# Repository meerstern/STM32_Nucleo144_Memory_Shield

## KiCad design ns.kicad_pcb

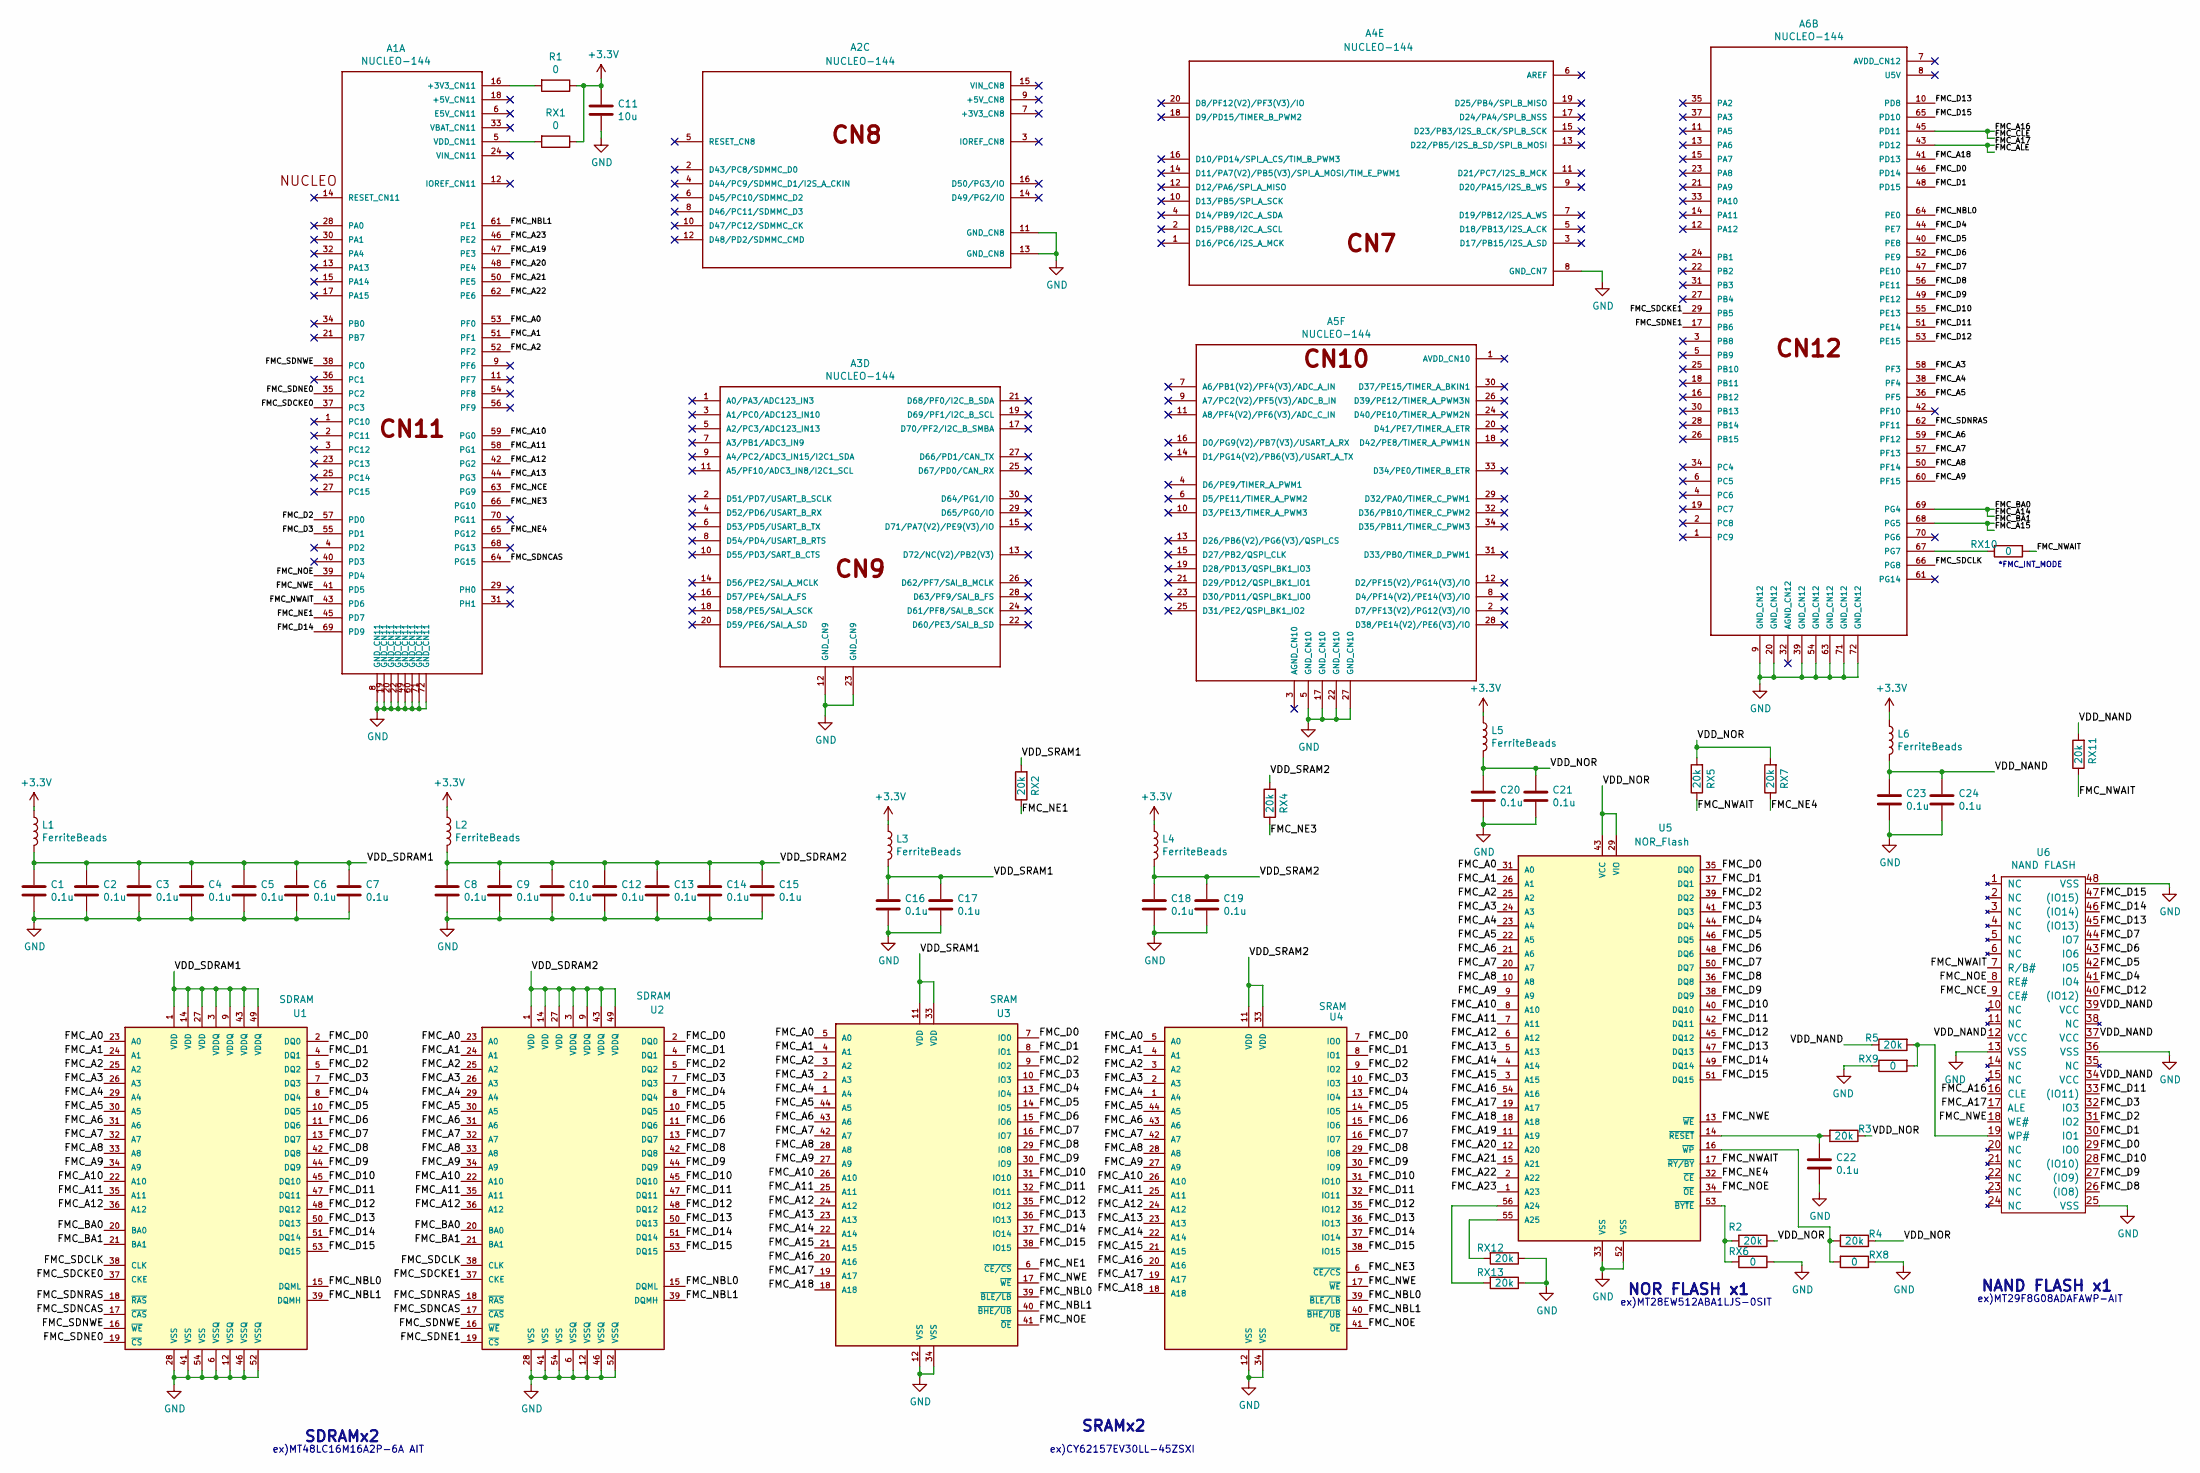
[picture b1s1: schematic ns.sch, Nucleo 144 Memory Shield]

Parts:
A1, A6: NUCLEO-144; PinSocket_2x36_P2.54mm_Vertical
A2: NUCLEO-144; PinSocket_2x08_P2.54mm_Vertical
A3: NUCLEO-144; PinSocket_2x15_P2.54mm_Vertical
A4: NUCLEO-144; PinSocket_2x10_P2.54mm_Vertical
A5: NUCLEO-144; PinSocket_2x17_P2.54mm_Vertical
C1, C2, C3, C4, C5, C6, C7, C8, C9, C10, C12, C13, C14, C15, C16, C17, C18, C19, C20, C21, C22, C23, C24: 0.1u; C_0603_1608Metric
C11: 10u; C_0805_2012Metric
L1, L2, L3, L4, L5, L6: FerriteBeads; L_0603_1608Metric
R1: 0; R_0603_1608Metric
R2, R3, R4, R5: 20k; R_0603_1608Metric
RX1, RX6, RX8, RX9, RX10: 0; R_0603_1608Metric
RX2, RX4, RX5, RX7, RX11, RX12, RX13: 20k; R_0603_1608Metric
U1, U2: SDRAM; TSOP-II-54_22.2x10.16mm_P0.8mm
U3, U4: SRAM; TSOP-II-44_10.16x18.41mm_P0.8mm
U5: NOR_Flash; TSOP-I-56_18.4x14mm_P0.5mm
U6: NAND FLASH; TSOP-I-48_18.4x12mm_P0.5mm

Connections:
+3V3: C11.1, L1.1, L2.1, L3.1, L4.1, L5.1, L6.1, R1.1, RX1.1
/FMC_A0: A1.53 (PF0), U1.23 (A0), U2.23 (A0), U3.5 (A0), U4.5 (A0), U5.31 (A0)
/FMC_A1: A1.51 (PF1), U1.24 (A1), U2.24 (A1), U3.4 (A1), U4.4 (A1), U5.26 (A1)
/FMC_A2: A1.52 (PF2), U1.25 (A2), U2.25 (A2), U3.3 (A2), U4.3 (A2), U5.25 (A2)
/FMC_A3: A6.58 (PG1), U1.26 (A3), U2.26 (A3), U3.2 (A3), U4.2 (A3), U5.24 (A3)
/FMC_A4: A6.38 (PC0), U1.29 (A4), U2.29 (A4), U3.1 (A4), U4.1 (A4), U5.23 (A4)
/FMC_A5: A6.36 (PC1), U1.30 (A5), U2.30 (A5), U3.44 (A5), U4.44 (A5), U5.22 (A5)
/FMC_A6: A6.59 (PG0), U1.31 (A6), U2.31 (A6), U3.43 (A6), U4.43 (A6), U5.21 (A6)
/FMC_A7: A6.57 (PD0), U1.32 (A7), U2.32 (A7), U3.42 (A7), U4.42 (A7), U5.20 (A7)
/FMC_A8: A6.50 (PE5), U1.33 (A8), U2.33 (A8), U3.28 (A8), U4.28 (A8), U5.10 (A8)
/FMC_A9: A6.60 (GND_CN11), U1.34 (A9), U2.34 (A9), U3.27 (A9), U4.27 (A9), U5.9 (A9)
/FMC_A10: A1.59 (PG0), U1.22 (A10), U2.22 (A10), U3.26 (A10), U4.26 (A10), U5.8 (A10)
/FMC_A11: A1.58 (PG1), U1.35 (A11), U2.35 (A11), U3.25 (A11), U4.25 (A11), U5.7 (A11)
/FMC_A12: A1.42 (PG2), U1.36 (A12), U2.36 (A12), U3.24 (A12), U4.24 (A12), U5.6 (A12)
/FMC_A13: A1.44 (PG3), U3.23 (A13), U4.23 (A13), U5.5 (A13)
/FMC_A14: A6.69 (PD9), U1.20 (BA0), U2.20 (BA0), U3.22 (A14), U4.22 (A14), U5.4 (A14)
/FMC_A15: A6.68 (PG13), U1.21 (BA1), U2.21 (BA1), U3.21 (A15), U4.21 (A15), U5.3 (A15)
/FMC_A16: A6.45 (PD7), U3.20 (A16), U4.20 (A16), U5.54 (A16), U6.16 (CLE)
/FMC_A17: A6.43 (PD6), U3.19 (A17), U4.19 (A17), U5.19 (A17), U6.17 (ALE)
/FMC_A18: A6.41 (PD5), U3.18 (A18), U4.18 (A18), U5.18 (A18)
/FMC_A19: A1.47 (PE3), U5.11 (A19)
/FMC_A20: A1.48 (PE4), U5.12 (A20)
/FMC_A21: A1.50 (PE5), U5.15 (A21)
/FMC_A22: A1.62 (PE6), U5.2 (A22)
/FMC_A23: A1.46 (PE2), U5.1 (A23)
/FMC_D0: A6.46 (PE2), U1.2 (DQ0), U2.2 (DQ0), U3.7 (IO0), U4.7 (IO0), U5.35 (DQ0), U6.29 (IO0)
/FMC_D1: A6.48 (PE4), U1.4 (DQ1), U2.4 (DQ1), U3.8 (IO1), U4.8 (IO1), U5.37 (DQ1), U6.30 (IO1)
/FMC_D2: A1.57 (PD0), U1.5 (DQ2), U2.5 (DQ2), U3.9 (IO2), U4.9 (IO2), U5.39 (DQ2), U6.31 (IO2)
/FMC_D3: A1.55 (PD1), U1.7 (DQ3), U2.7 (DQ3), U3.10 (IO3), U4.10 (IO3), U5.41 (DQ3), U6.32 (IO3)
/FMC_D4: A6.44 (PG3), U1.8 (DQ4), U2.8 (DQ4), U3.13 (IO4), U4.13 (IO4), U5.44 (DQ4), U6.41 (IO4)
/FMC_D5: A6.40 (PD3), U1.10 (DQ5), U2.10 (DQ5), U3.14 (IO5), U4.14 (IO5), U5.46 (DQ5), U6.42 (IO5)
/FMC_D6: A6.52 (PF2), U1.11 (DQ6), U2.11 (DQ6), U3.15 (IO6), U4.15 (IO6), U5.48 (DQ6), U6.43 (IO6)
/FMC_D7: A6.47 (PE3), U1.13 (DQ7), U2.13 (DQ7), U3.16 (IO7), U4.16 (IO7), U5.50 (DQ7), U6.44 (IO7)
/FMC_D8: A6.56 (PF9), U1.42 (DQ8), U2.42 (DQ8), U3.29 (IO8), U4.29 (IO8), U5.36 (DQ8), U6.26 ((IO8))
/FMC_D9: A6.49 (GND_CN11), U1.44 (DQ9), U2.44 (DQ9), U3.30 (IO9), U4.30 (IO9), U5.38 (DQ9), U6.27 ((IO9))
/FMC_D10: A6.55 (PD1), U1.45 (DQ10), U2.45 (DQ10), U3.31 (IO10), U4.31 (IO10), U5.40 (DQ10), U6.28 ((IO10))
/FMC_D11: A6.51 (PF1), U1.47 (DQ11), U2.47 (DQ11), U3.32 (IO11), U4.32 (IO11), U5.42 (DQ11), U6.33 ((IO11))
/FMC_D12: A6.53 (PF0), U1.48 (DQ12), U2.48 (DQ12), U3.35 (IO12), U4.35 (IO12), U5.45 (DQ12), U6.40 ((IO12))
/FMC_D13: A6.10 (PD8), U1.50 (DQ13), U2.50 (DQ13), U3.36 (IO13), U4.36 (IO13), U5.47 (DQ13), U6.45 ((IO13))
/FMC_D14: A1.69 (PD9), U1.51 (DQ14), U2.51 (DQ14), U3.37 (IO14), U4.37 (IO14), U5.49 (DQ14), U6.46 ((IO14))
/FMC_D15: A6.65 (PG12), U1.53 (DQ15), U2.53 (DQ15), U3.38 (IO15), U4.38 (IO15), U5.51 (DQ15), U6.47 ((IO15))
/FMC_NBL0: A6.64 (PG15), U1.15 (DQML), U2.15 (DQML), U3.39 (~BLE/LB~), U4.39 (~BLE/LB~)
/FMC_NBL1: A1.61 (PE1), U1.39 (DQMH), U2.39 (DQMH), U3.40 (~BHE/UB~), U4.40 (~BHE/UB~)
/FMC_NCE: A1.63 (PG9), U6.9 (CE#)
/FMC_NE1: A1.45 (PD7), RX2.1, U3.6 (~CE/CS~)
/FMC_NE3: A1.66 (PG10), RX4.1, U4.6 (~CE/CS~)
/FMC_NE4: A1.65 (PG12), RX7.1, U5.32 (~CE~)
/FMC_NOE: A1.39 (PD4), U3.41 (~OE~), U4.41 (~OE~), U5.34 (~OE~), U6.8 (RE#)
/FMC_NWAIT: A1.43 (PD6), RX5.1, RX10.2, RX11.1, U5.17 (~RY/BY~), U6.7 (R/B#)
/FMC_NWE: A1.41 (PD5), U3.17 (~WE~), U4.17 (~WE~), U5.13 (~WE~), U6.18 (WE#)
/FMC_SDCKE0: A1.37 (PC3), U1.37 (CKE)
/FMC_SDCKE1: A6.29 (PH0), U2.37 (CKE)
/FMC_SDCLK: A6.66 (PG10), U1.38 (CLK), U2.38 (CLK)
/FMC_SDNCAS: A1.64 (PG15), U1.17 (~CAS~), U2.17 (~CAS~)
/FMC_SDNE0: A1.35 (PC2), U1.19 (~CS~)
/FMC_SDNE1: A6.17 (PA15), U2.19 (~CS~)
/FMC_SDNRAS: A6.62 (PE6), U1.18 (~RAS~), U2.18 (~RAS~)
/FMC_SDNWE: A1.38 (PC0), U1.16 (~WE~), U2.16 (~WE~)
/VDD_NAND: C23.1, C24.1, L6.2, R5.1, RX11.2, U6.12 (VCC), U6.34 (VCC), U6.37 (VCC), U6.39 (VCC)
/VDD_NOR: C20.1, C21.1, L5.2, R2.1, R3.1, R4.1, RX5.2, RX7.2, U5.29 (VIO), U5.43 (VCC)
/VDD_SDRAM1: C1.1, C2.1, C3.1, C4.1, C5.1, C6.1, C7.1, L1.2, U1.1 (VDD), U1.3 (VDDQ), U1.9 (VDDQ), U1.14 (VDD), U1.27 (VDD), U1.43 (VDDQ), U1.49 (VDDQ)
/VDD_SDRAM2: C8.1, C9.1, C10.1, C12.1, C13.1, C14.1, C15.1, L2.2, U2.1 (VDD), U2.3 (VDDQ), U2.9 (VDDQ), U2.14 (VDD), U2.27 (VDD), U2.43 (VDDQ), U2.49 (VDDQ)
/VDD_SRAM1: C16.1, C17.1, L3.2, RX2.2, U3.11 (VDD), U3.33 (VDD)
/VDD_SRAM2: C18.1, C19.1, L4.2, RX4.2, U4.11 (VDD), U4.33 (VDD)
GND: A1.8 (GND_CN11), A1.19 (GND_CN11), A1.20 (GND_CN11), A1.22 (GND_CN11), A1.49 (GND_CN11), A1.60 (GND_CN11), A1.71 (GND_CN11), A1.72 (GND_CN11), A2.11 (PF7), A2.13 (PA13), A3.12 (IOREF_CN11), A3.23 (PC13), A4.8 (GND_CN11), A5.5 (VDD_CN11), A5.17 (PA15), A5.22 (GND_CN11), A5.27 (PC15), A6.9 (PF6), A6.20 (GND_CN11), A6.39 (PD4), A6.54 (PF8), A6.63 (PG9), A6.71 (GND_CN11), A6.72 (GND_CN11), C1.2, C2.2, C3.2, C4.2, C5.2, C6.2, C7.2, C8.2, C9.2, C10.2, C11.2, C12.2, C13.2, C14.2, C15.2, C16.2, C17.2, C18.2, C19.2, C20.2, C21.2, C22.2, C23.2, C24.2, RX6.1, RX8.1, RX9.1, RX12.1, RX13.1, U1.6 (VSSQ), U1.12 (VSSQ), U1.28 (VSS), U1.41 (VSS), U1.46 (VSSQ), U1.52 (VSSQ), U1.54 (VSS), U2.6 (VSSQ), U2.12 (VSSQ), U2.28 (VSS), U2.41 (VSS), U2.46 (VSSQ), U2.52 (VSSQ), U2.54 (VSS), U3.12 (VSS), U3.34 (VSS), U4.12 (VSS), U4.34 (VSS), U5.33 (VSS), U5.52 (VSS), U6.13 (VSS), U6.25 (VSS), U6.36 (VSS), U6.48 (VSS)
unnamed: A1.5 (VDD_CN11), RX1.2
unnamed: A1.16 (+3V3_CN11), R1.2
unnamed: A6.67 (PG7), RX10.1
unnamed: C22.1, R3.2, U5.14 (~RESET~)
unnamed: R2.2, RX6.2, U5.53 (~BYTE~)
unnamed: R4.2, RX8.2, U5.16 (~WP~)
unnamed: R5.2, RX9.2, U6.19 (WP#)
unnamed: RX12.2, U5.55 (A25)
unnamed: RX13.2, U5.56 (A24)

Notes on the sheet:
SDRAMx2
SRAMx2
NOR FLASH x1
NAND FLASH x1
*FMC_INT_MODE
ex)CY62157EV30LL-45ZSXI
ex)MT28EW512ABA1LJS-0SIT
ex)MT29F8G08ADAFAWP-AIT
ex)MT48LC16M16A2P-6A AIT

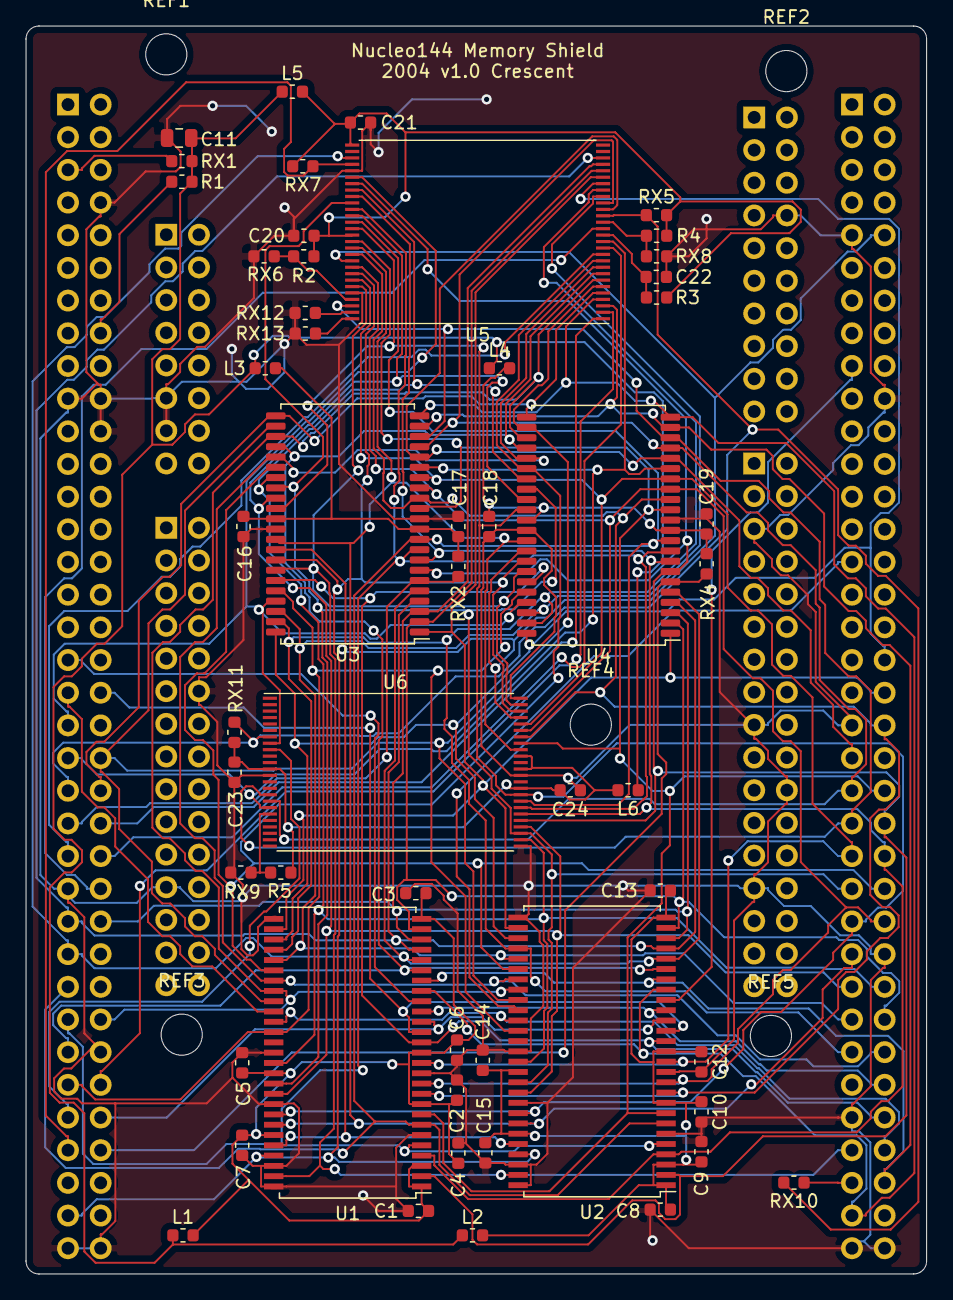
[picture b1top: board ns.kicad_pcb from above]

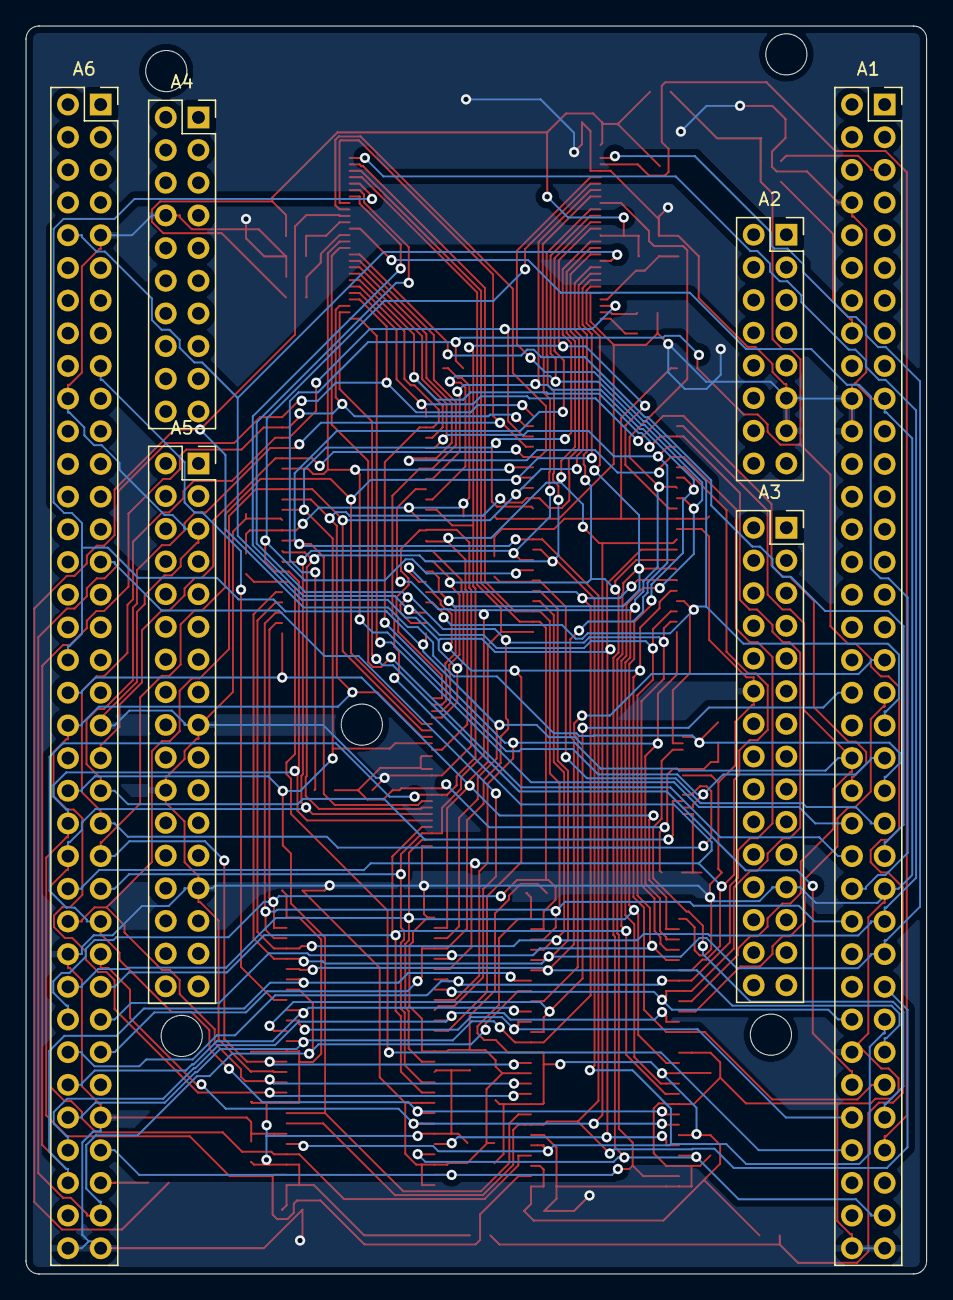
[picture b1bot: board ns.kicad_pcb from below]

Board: 2 copper layers, 70.0 x 97.0 mm, 64 parts (6 on the bottom side), 74 nets.

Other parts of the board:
REF1, REF2, REF3, REF4, REF5: MountingHole_3.2mm_M3

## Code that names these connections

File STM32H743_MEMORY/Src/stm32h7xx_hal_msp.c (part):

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    __HAL_RCC_GPIOB_CLK_ENABLE();
    __HAL_RCC_GPIOG_CLK_ENABLE();
    /**ETH GPIO Configuration    
    PC1     ------> ETH_MDC
    PA1     ------> ETH_REF_CLK
    PA2     ------> ETH_MDIO
    PA7     ------> ETH_CRS_DV
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    PC5     ------> ETH_RXD1
    PB13     ------> ETH_TXD1
    PG11     ------> ETH_TX_EN
    PG13     ------> ETH_TXD0 
    */
    GPIO_InitStruct.Pin = GPIO_PIN_1|GPIO_PIN_4|GPIO_PIN_5;
    GPIO_InitStruct.Mode = GPIO_MODE_AF_PP;
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    __HAL_RCC_ETH1RX_CLK_DISABLE();
  
    /**ETH GPIO Configuration    
    PC1     ------> ETH_MDC
    PA1     ------> ETH_REF_CLK
    PA2     ------> ETH_MDIO
    PA7     ------> ETH_CRS_DV
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    PC5     ------> ETH_RXD1
    PB13     ------> ETH_TXD1
    PG11     ------> ETH_TX_EN
    PG13     ------> ETH_TXD0 
    */
    HAL_GPIO_DeInit(GPIOC, GPIO_PIN_1|GPIO_PIN_4|GPIO_PIN_5);

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  __HAL_RCC_FMC_CLK_ENABLE();
  
  /** FMC GPIO Configuration  
  PE2   ------> FMC_A23
  PE3   ------> FMC_A19
  PE4   ------> FMC_A20
  PE5   ------> FMC_A21
  PE6   ------> FMC_A22
  PF0   ------> FMC_A0
  PF1   ------> FMC_A1
  PF2   ------> FMC_A2
  PF3   ------> FMC_A3
  PF4   ------> FMC_A4
  PF5   ------> FMC_A5
  PC0   ------> FMC_SDNWE
  PC2_C   ------> FMC_SDNE0
  PC3_C   ------> FMC_SDCKE0
  PF11   ------> FMC_SDNRAS
  PF12   ------> FMC_A6
  PF13   ------> FMC_A7
  PF14   ------> FMC_A8
  PF15   ------> FMC_A9
  PG0   ------> FMC_A10
  PG1   ------> FMC_A11
  PE7   ------> FMC_D4
  PE8   ------> FMC_D5
  PE9   ------> FMC_D6
  PE10   ------> FMC_D7
  PE11   ------> FMC_D8
  PE12   ------> FMC_D9
  PE13   ------> FMC_D10
  PE14   ------> FMC_D11
  PE15   ------> FMC_D12
  PD8   ------> FMC_D13
  PD9   ------> FMC_D14
  PD10   ------> FMC_D15
  PD11   ------> FMC_CLE
  PD11   ------> FMC_A16
  PD12   ------> FMC_ALE
  PD12   ------> FMC_A17
  PD13   ------> FMC_A18
  PD14   ------> FMC_D0
  PD15   ------> FMC_D1
  PG2   ------> FMC_A12
  PG3   ------> FMC_A13
  PG4   ------> FMC_BA0
  PG4   ------> FMC_A14
  PG5   ------> FMC_BA1
  PG5   ------> FMC_A15
  PG8   ------> FMC_SDCLK
  PD0   ------> FMC_D2
  PD1   ------> FMC_D3
  PD4   ------> FMC_NOE
  PD5   ------> FMC_NWE
  PD6   ------> FMC_NWAIT
  PD7   ------> FMC_NE1
  PG9   ------> FMC_NCE
  PG10   ------> FMC_NE3
  PG12   ------> FMC_NE4
  PG15   ------> FMC_SDNCAS
  PB5   ------> FMC_SDCKE1
  PB6   ------> FMC_SDNE1
  PE0   ------> FMC_NBL0
  PE1   ------> FMC_NBL1
  */
  GPIO_InitStruct.Pin = GPIO_PIN_2|GPIO_PIN_3|GPIO_PIN_4|GPIO_PIN_5 
                          |GPIO_PIN_6|GPIO_PIN_7|GPIO_PIN_8|GPIO_PIN_9 
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  __HAL_RCC_FMC_CLK_DISABLE();
  
  /** FMC GPIO Configuration  
  PE2   ------> FMC_A23
  PE3   ------> FMC_A19
  PE4   ------> FMC_A20
  PE5   ------> FMC_A21
  PE6   ------> FMC_A22
  PF0   ------> FMC_A0
  PF1   ------> FMC_A1
  PF2   ------> FMC_A2
  PF3   ------> FMC_A3
  PF4   ------> FMC_A4
  PF5   ------> FMC_A5
  PC0   ------> FMC_SDNWE
  PC2_C   ------> FMC_SDNE0
  PC3_C   ------> FMC_SDCKE0
  PF11   ------> FMC_SDNRAS
  PF12   ------> FMC_A6
  PF13   ------> FMC_A7
  PF14   ------> FMC_A8
  PF15   ------> FMC_A9
  PG0   ------> FMC_A10
  PG1   ------> FMC_A11
  PE7   ------> FMC_D4
  PE8   ------> FMC_D5
  PE9   ------> FMC_D6
  PE10   ------> FMC_D7
  PE11   ------> FMC_D8
  PE12   ------> FMC_D9
  PE13   ------> FMC_D10
  PE14   ------> FMC_D11
  PE15   ------> FMC_D12
  PD8   ------> FMC_D13
  PD9   ------> FMC_D14
  PD10   ------> FMC_D15
  PD11   ------> FMC_CLE
  PD11   ------> FMC_A16
  PD12   ------> FMC_ALE
  PD12   ------> FMC_A17
  PD13   ------> FMC_A18
  PD14   ------> FMC_D0
  PD15   ------> FMC_D1
  PG2   ------> FMC_A12
  PG3   ------> FMC_A13
  PG4   ------> FMC_BA0
  PG4   ------> FMC_A14
  PG5   ------> FMC_BA1
  PG5   ------> FMC_A15
  PG8   ------> FMC_SDCLK
  PD0   ------> FMC_D2
  PD1   ------> FMC_D3
  PD4   ------> FMC_NOE
  PD5   ------> FMC_NWE
  PD6   ------> FMC_NWAIT
  PD7   ------> FMC_NE1
  PG9   ------> FMC_NCE
  PG10   ------> FMC_NE3
  PG12   ------> FMC_NE4
  PG15   ------> FMC_SDNCAS
  PB5   ------> FMC_SDCKE1
  PB6   ------> FMC_SDNE1
  PE0   ------> FMC_NBL0
  PE1   ------> FMC_NBL1
  */
  HAL_GPIO_DeInit(GPIOE, GPIO_PIN_2|GPIO_PIN_3|GPIO_PIN_4|GPIO_PIN_5 
                          |GPIO_PIN_6|GPIO_PIN_7|GPIO_PIN_8|GPIO_PIN_9 
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
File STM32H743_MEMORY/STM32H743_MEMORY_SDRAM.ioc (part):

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Mcu.Name=STM32H743ZITx
Mcu.Package=LQFP144
Mcu.UserName=STM32H743ZITx
PA1.Mode=RMII
PA1.Signal=ETH_REF_CLK
PA11.Signal=USB_OTG_FS_DM
PA12.Signal=USB_OTG_FS_DP
PA2.Mode=RMII
PA2.Signal=ETH_MDIO
PA7.Mode=RMII
PA7.Signal=ETH_CRS_DV
PA8.Signal=USB_OTG_FS_SOF
PA9.Signal=USB_OTG_FS_VBUS
PB0.GPIOParameters=GPIO_Label
PB0.GPIO_Label=LD1 [Green Led]
PB0.Signal=GPIO_Output
PB10.Mode=Asynchronous
PB10.Signal=USART3_TX
PB11.Mode=Asynchronous
PB11.Signal=USART3_RX
PB13.Mode=RMII
PB13.Signal=ETH_TXD1
PB14.GPIOParameters=GPIO_Label
PB14.GPIO_Label=LD3 [Red Led]
PB14.Signal=GPIO_Output
PB5.Mode=SdramChipSelect2_2
PB5.Signal=FMC_SDCKE1
PB6.Mode=SdramChipSelect2_2
PB6.Signal=FMC_SDNE1
PC0.Signal=FMC_SDNWE
PC1.Mode=RMII
PC1.Signal=ETH_MDC
PC13.GPIOParameters=GPIO_Label
PC13.GPIO_Label=B1 [Blue PushButton]
PC13.Signal=GPIO_Input
PC14-OSC32_IN\ (OSC32_IN).Mode=LSE-External-Oscillator
PC14-OSC32_IN\ (OSC32_IN).Signal=RCC_OSC32_IN
PC15-OSC32_OUT\ (OSC32_OUT).Mode=LSE-External-Oscillator
PC15-OSC32_OUT\ (OSC32_OUT).Signal=RCC_OSC32_OUT
PC2_C.Mode=SdramChipSelect1_1
PC2_C.Signal=FMC_SDNE0
PC3_C.Mode=SdramChipSelect1_1
PC3_C.Signal=FMC_SDCKE0
PC4.Mode=RMII
PC4.Signal=ETH_RXD0
PC5.Mode=RMII
PC5.Signal=ETH_RXD1
PD0.Signal=FMC_D2_DA2
PD1.Signal=FMC_D3_DA3
PD10.Signal=FMC_D15_DA15
PD11.Signal=FMC_A16_CLE
PD12.Signal=FMC_A17_ALE
PD13.Signal=FMC_A18
PD14.Signal=FMC_D0_DA0
PD15.Signal=FMC_D1_DA1
PD4.Signal=FMC_NOE
PD5.Signal=FMC_NWE
PD6.Signal=FMC_NWAIT
PD7.Mode=NorPsramChipSelect1_1
PD7.Signal=FMC_NE1
PD8.Signal=FMC_D13_DA13
PD9.Signal=FMC_D14_DA14
PE0.Signal=FMC_NBL0
PE1.Signal=FMC_NBL1
PE10.Signal=FMC_D7_DA7
PE11.Signal=FMC_D8_DA8
PE12.Signal=FMC_D9_DA9
PE13.Signal=FMC_D10_DA10
PE14.Signal=FMC_D11_DA11
PE15.Signal=FMC_D12_DA12
PE2.Signal=FMC_A23
PE3.Signal=FMC_A19
PE4.Signal=FMC_A20
PE5.Signal=FMC_A21
PE6.Signal=FMC_A22
PE7.Signal=FMC_D4_DA4
PE8.Signal=FMC_D5_DA5
PE9.Signal=FMC_D6_DA6
PF0.Signal=FMC_A0
PF1.Signal=FMC_A1
PF11.Signal=FMC_SDNRAS
PF12.Signal=FMC_A6
PF13.Signal=FMC_A7
PF14.Signal=FMC_A8
PF15.Signal=FMC_A9
PF2.Signal=FMC_A2
PF3.Signal=FMC_A3
PF4.Signal=FMC_A4
PF5.Signal=FMC_A5
PG0.Signal=FMC_A10
PG1.Signal=FMC_A11
PG10.Mode=NorPsramChipSelect3_2
PG10.Signal=FMC_NE3
PG11.Mode=RMII
PG11.Signal=ETH_TX_EN
PG12.Mode=NorPsramChipSelect4_3
PG12.Signal=FMC_NE4
PG13.Mode=RMII
PG13.Signal=ETH_TXD0
PG15.Signal=FMC_SDNCAS
PG2.Signal=FMC_A12
PG3.Signal=FMC_A13
PG4.Signal=FMC_A14_BA0
PG5.Signal=FMC_A15_BA1
PG8.Signal=FMC_SDCLK
PG9.Mode=NandChipSelect3_1
PG9.Signal=FMC_NCE
PH0-OSC_IN\ (PH0).Mode=HSE-External-Clock-Source
PH0-OSC_IN\ (PH0).Signal=RCC_OSC_IN
PH1-OSC_OUT\ (PH1).Signal=RCC_OSC_OUT
RCC.HSE_VALUE=8000000
RCC.SYSCLKFreq_VALUE=400000000
RCC.SYSCLKSource=RCC_SYSCLKSOURCE_PLLCLK
board=NUCLEO-H743ZI2
boardIOC=true

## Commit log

2020-06-07 Add PCB data
2020-06-28 Add img files
2020-09-20 Add sample code with CubeMX

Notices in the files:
STM32H743_MEMORY/Src/stm32h7xx_hal_msp.c:
© Copyright (c) 2020 STMicroelectronics.
All rights reserved.
This software component is licensed by ST under BSD 3-Clause license,
the "License"; You may not use this file except in compliance with the
License. You may obtain a copy of the License at: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
(C) COPYRIGHT STMicroelectronics *****END OF FILE
